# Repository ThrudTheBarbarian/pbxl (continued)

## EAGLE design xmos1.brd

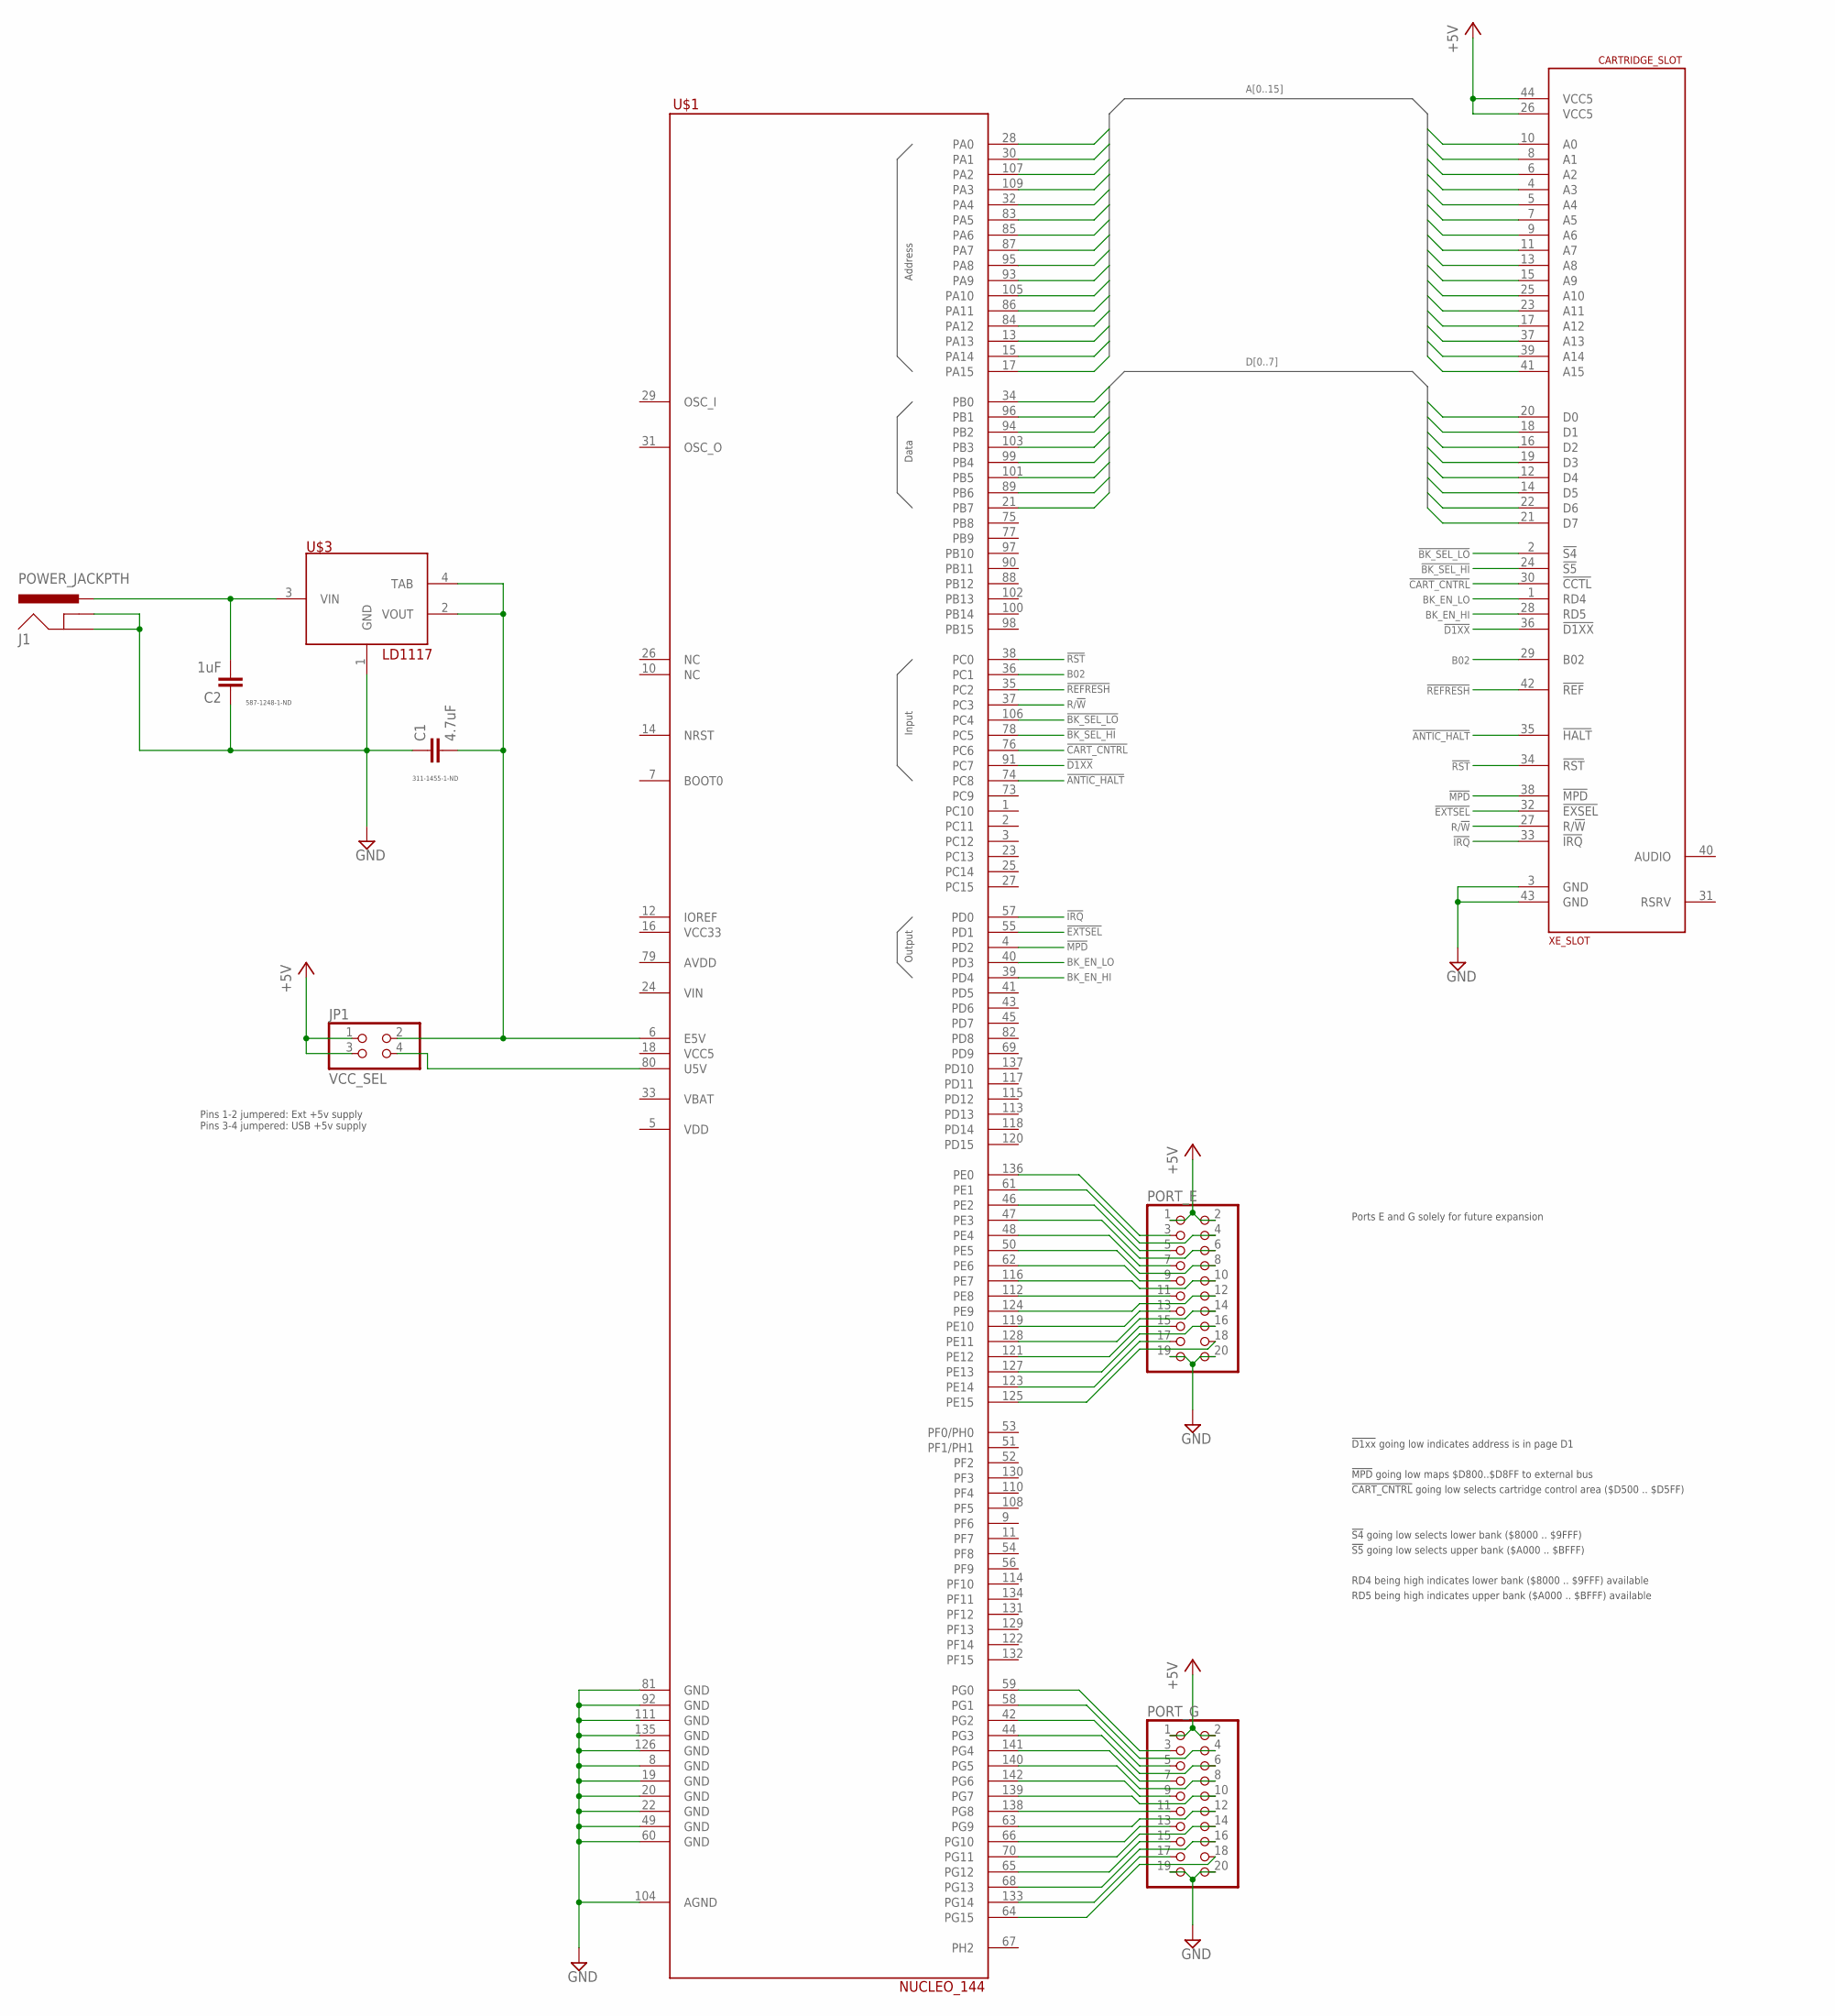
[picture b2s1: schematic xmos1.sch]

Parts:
C1: 4.7uF; C0603
C2: 1uF; C0603
CARTRIDGE_SLOT: XE_SLOT
J1: POWER_JACKPTH; POWER_JACK_PTH
JP1: VCC_SEL; 2X02
PORT_E: PINHD-2X10; 2X10
PORT_G: PINHD-2X10; 2X10
U$1: NUCLEO_144
U$3: LD1117; SOT223

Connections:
!ANTIC_HALT!: CARTRIDGE_SLOT.35 (!HALT!), U$1.74 (PC8)
!BK_SEL_HI!: CARTRIDGE_SLOT.24 (!S5!), U$1.78 (PC5)
!BK_SEL_LO!: CARTRIDGE_SLOT.2 (!S4!), U$1.106 (PC4)
!CART_CNTRL!: CARTRIDGE_SLOT.30 (!CCTL!), U$1.76 (PC6)
!D1XX!: CARTRIDGE_SLOT.36 (!D1XX!), U$1.91 (PC7)
!EXTSEL!: CARTRIDGE_SLOT.32 (!EXSEL!), U$1.55 (PD1)
!IRQ!: CARTRIDGE_SLOT.33 (!IRQ!), U$1.57 (PD0)
!MPD!: CARTRIDGE_SLOT.38 (!MPD!), U$1.4 (PD2)
!REFRESH!: CARTRIDGE_SLOT.42 (!REF!), U$1.35 (PC2)
!RST!: CARTRIDGE_SLOT.34 (!RST!), U$1.38 (PC0)
+5V: CARTRIDGE_SLOT.26 (VCC5), CARTRIDGE_SLOT.44 (VCC5), JP1.1, JP1.3, PORT_E.1, PORT_E.2, PORT_G.1, PORT_G.2
A0: CARTRIDGE_SLOT.10 (A0), U$1.28 (PA0)
A1: CARTRIDGE_SLOT.8 (A1), U$1.30 (PA1)
A2: CARTRIDGE_SLOT.6 (A2), U$1.107 (PA2)
A3: CARTRIDGE_SLOT.4 (A3), U$1.109 (PA3)
A4: CARTRIDGE_SLOT.5 (A4), U$1.32 (PA4)
A5: CARTRIDGE_SLOT.7 (A5), U$1.83 (PA5)
A6: CARTRIDGE_SLOT.9 (A6), U$1.85 (PA6)
A7: CARTRIDGE_SLOT.11 (A7), U$1.87 (PA7)
A8: CARTRIDGE_SLOT.13 (A8), U$1.95 (PA8)
A9: CARTRIDGE_SLOT.15 (A9), U$1.93 (PA9)
A10: CARTRIDGE_SLOT.25 (A10), U$1.105 (PA10)
A11: CARTRIDGE_SLOT.23 (A11), U$1.86 (PA11)
A12: CARTRIDGE_SLOT.17 (A12), U$1.84 (PA12)
A13: CARTRIDGE_SLOT.37 (A13), U$1.13 (PA13)
A14: CARTRIDGE_SLOT.39 (A14), U$1.15 (PA14)
A15: CARTRIDGE_SLOT.41 (A15), U$1.17 (PA15)
B02: CARTRIDGE_SLOT.29 (B02), U$1.36 (PC1)
BK_EN_HI: CARTRIDGE_SLOT.28 (RD5), U$1.39 (PD4)
BK_EN_LO: CARTRIDGE_SLOT.1 (RD4), U$1.40 (PD3)
D0: CARTRIDGE_SLOT.20 (D0), U$1.34 (PB0)
D1: CARTRIDGE_SLOT.18 (D1), U$1.96 (PB1)
D2: CARTRIDGE_SLOT.16 (D2), U$1.94 (PB2)
D3: CARTRIDGE_SLOT.19 (D3), U$1.103 (PB3)
D4: CARTRIDGE_SLOT.12 (D4), U$1.99 (PB4)
D5: CARTRIDGE_SLOT.14 (D5), U$1.101 (PB5)
D6: CARTRIDGE_SLOT.22 (D6), U$1.89 (PB6)
D7: CARTRIDGE_SLOT.21 (D7), U$1.21 (PB7)
GND: C1.1, C2.1, CARTRIDGE_SLOT.3 (GND), CARTRIDGE_SLOT.43 (GND), J1.GND, J1.GNDBREAK, PORT_E.19, PORT_E.20, PORT_G.19, PORT_G.20, U$1.8 (GND), U$1.19 (GND), U$1.20 (GND), U$1.22 (GND), U$1.49 (GND), U$1.60 (GND), U$1.81 (GND), U$1.92 (GND), U$1.104 (AGND), U$1.111 (GND), U$1.126 (GND), U$1.135 (GND), U$3.1 (GND)
unnamed: C1.2, JP1.2, U$1.6 (E5V), U$3.2 (VOUT), U$3.4 (TAB)
unnamed: JP1.4, U$1.80 (U5V)
unnamed: PORT_E.3, U$1.136 (PE0)
unnamed: PORT_E.4, U$1.61 (PE1)
unnamed: PORT_E.5, U$1.46 (PE2)
unnamed: PORT_E.6, U$1.47 (PE3)
unnamed: PORT_E.7, U$1.48 (PE4)
unnamed: PORT_E.8, U$1.50 (PE5)
unnamed: PORT_E.9, U$1.62 (PE6)
unnamed: PORT_E.10, U$1.116 (PE7)
unnamed: PORT_E.11, U$1.112 (PE8)
unnamed: PORT_E.12, U$1.124 (PE9)
unnamed: PORT_E.13, U$1.119 (PE10)
unnamed: PORT_E.14, U$1.128 (PE11)
unnamed: PORT_E.15, U$1.121 (PE12)
unnamed: PORT_E.16, U$1.127 (PE13)
unnamed: PORT_E.17, U$1.123 (PE14)
unnamed: PORT_E.18, U$1.125 (PE15)
unnamed: PORT_G.3, U$1.59 (PG0)
unnamed: PORT_G.4, U$1.58 (PG1)
unnamed: PORT_G.5, U$1.42 (PG2)
unnamed: PORT_G.6, U$1.44 (PG3)
unnamed: PORT_G.7, U$1.141 (PG4)
unnamed: PORT_G.8, U$1.140 (PG5)
unnamed: PORT_G.9, U$1.142 (PG6)
unnamed: PORT_G.11, U$1.138 (PG8)
unnamed: C2.2, J1.PWR, U$3.3 (VIN)
unnamed: PORT_G.12, U$1.63 (PG9)
unnamed: PORT_G.13, U$1.66 (PG10)
unnamed: PORT_G.14, U$1.70 (PG11)
unnamed: PORT_G.15, U$1.65 (PG12)
unnamed: PORT_G.16, U$1.68 (PG13)
unnamed: PORT_G.17, U$1.133 (PG14)
unnamed: PORT_G.18, U$1.64 (PG15)
PORT_G: PORT_G.10, U$1.139 (PG7)
R/!W!: CARTRIDGE_SLOT.27 (R/!W!), U$1.37 (PC3)

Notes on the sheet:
!MPD! going low maps $D800..$D8FF to external bus
!S4! going low selects lower bank ($8000 .. $9FFF)
!S5! going low selects upper bank ($A000 .. $BFFF)
!CART_CNTRL! going low selects cartridge control area ($D500 .. $D5FF)
!D1xx! going low indicates address is in page D1
RD4 being high indicates lower bank ($8000 .. $9FFF) available
RD5 being high indicates upper bank ($A000 .. $BFFF) available
Output
Input
Data
Address
Pins 1-2 jumpered: Ext +5v supply Pins 3-4 jumpered: USB +5v supply
Ports E and G solely for future expansion
311-1455-1-ND
587-1248-1-ND

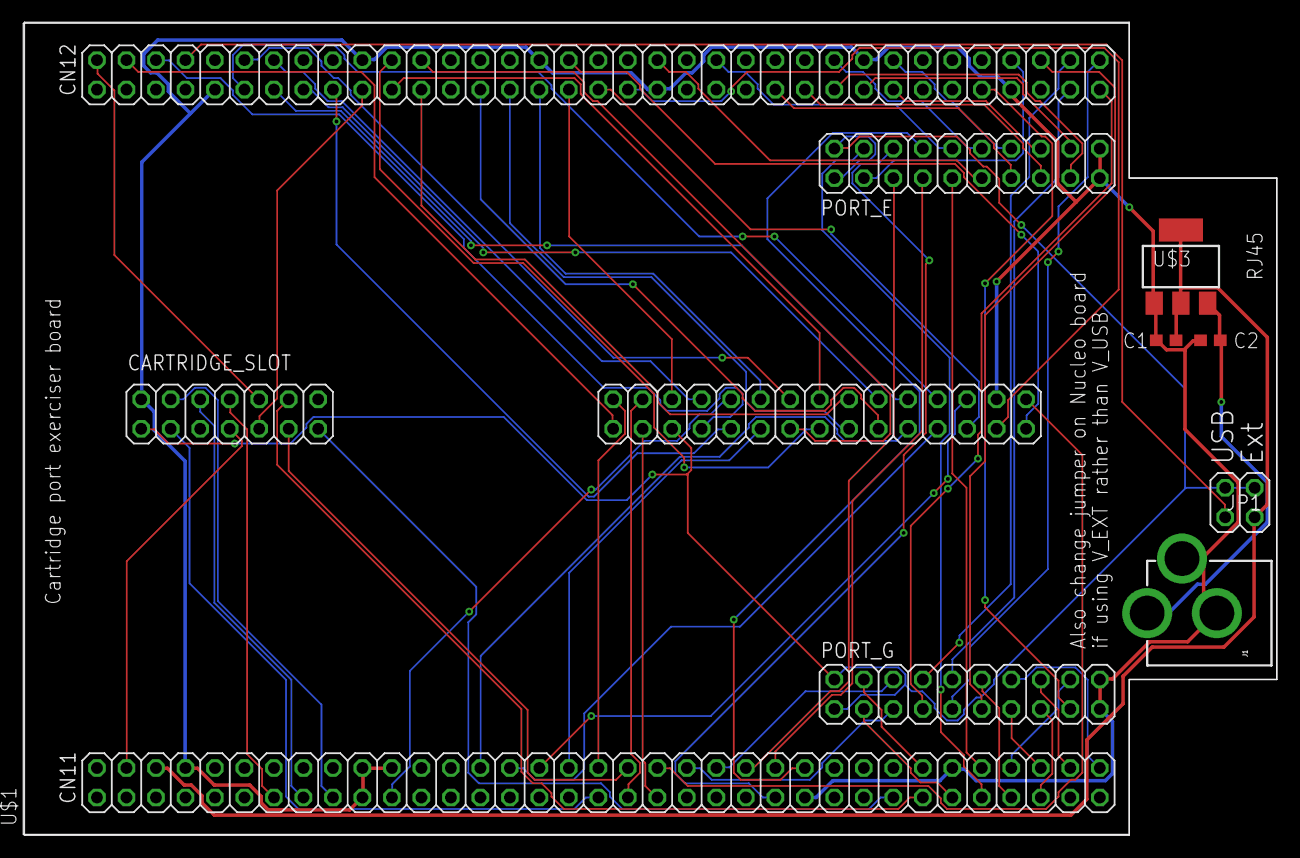
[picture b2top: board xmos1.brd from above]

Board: 2 copper layers, 108.0 x 69.8 mm, 9 parts (0 on the bottom side), 75 nets.

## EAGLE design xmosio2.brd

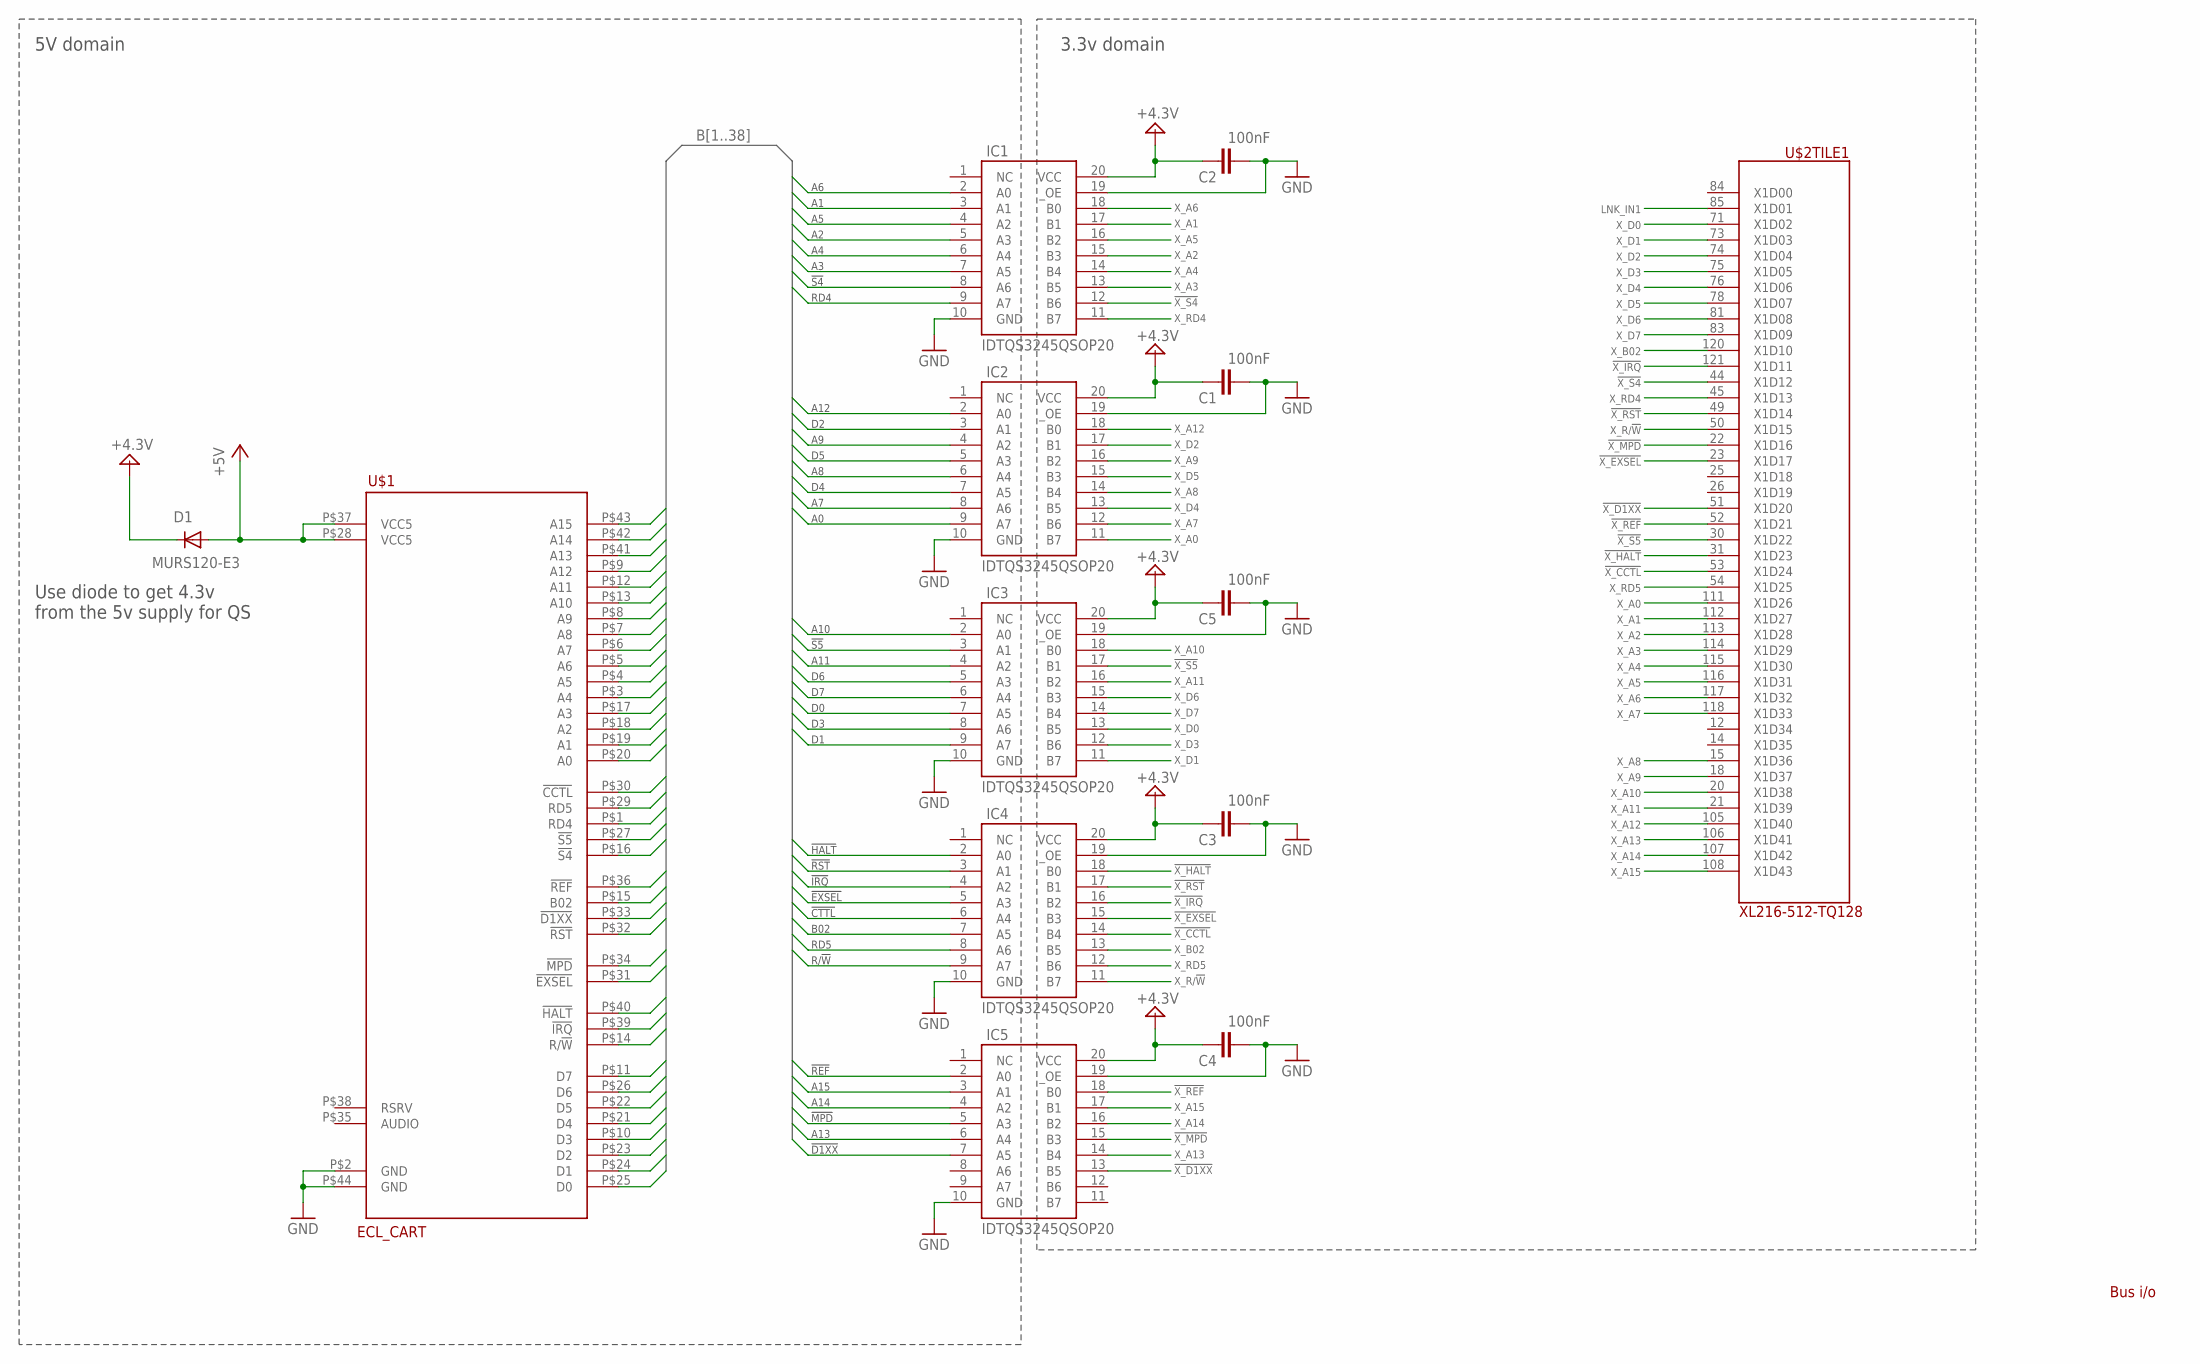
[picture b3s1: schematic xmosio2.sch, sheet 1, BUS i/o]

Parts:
C1, C2, C3, C4, C5: 100nF; C0603
D1: MURS120-E3; SMB
IC1, IC2, IC3, IC4, IC5: IDTQS3245QSOP20; QSOP20
U$1: ECL_CART
U$2: XL216-512-TQ128; TQFP128

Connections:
!X_CCTL!: IC4.14 (B4), U$2.53 (X1D24)
!X_D1XX!: IC5.13 (B5), U$2.51 (X1D20)
!X_EXSEL!: IC4.15 (B3), U$2.23 (X1D17)
!X_HALT!: IC4.18 (B0), U$2.31 (X1D23)
!X_IRQ!: IC4.16 (B2), U$2.121 (X1D11)
!X_MPD!: IC5.15 (B3), U$2.22 (X1D16)
!X_REF!: IC5.18 (B0), U$2.52 (X1D21)
!X_RST!: IC4.17 (B1), U$2.49 (X1D14)
!X_S4!: IC1.12 (B6), U$2.44 (X1D12)
!X_S5!: IC3.17 (B1), U$2.30 (X1D22)
+4.3V: C1.1, C2.1, C3.1, C4.1, C5.1, D1.C, IC1.20 (VCC), IC2.20 (VCC), IC3.20 (VCC), IC4.20 (VCC), IC5.20 (VCC)
+5V: D1.A, U$1.P$28 (VCC5), U$1.P$37 (VCC5); also elsewhere on the board
B1: IC1.9 (A7), U$1.P$1 (RD4)
B2: IC1.8 (A6), U$1.P$16 (!S4!)
B3: IC1.7 (A5), U$1.P$17 (A3)
B4: IC1.6 (A4), U$1.P$3 (A4)
B5: IC1.5 (A3), U$1.P$18 (A2)
B6: IC1.4 (A2), U$1.P$4 (A5)
B7: IC1.3 (A1), U$1.P$19 (A1)
B8: IC1.2 (A0), U$1.P$5 (A6)
B9: IC2.9 (A7), U$1.P$20 (A0)
B10: IC2.8 (A6), U$1.P$6 (A7)
B11: IC2.7 (A5), U$1.P$21 (D4)
B12: IC2.6 (A4), U$1.P$7 (A8)
B13: IC2.5 (A3), U$1.P$22 (D5)
B14: IC2.4 (A2), U$1.P$8 (A9)
B15: IC2.3 (A1), U$1.P$23 (D2)
B16: IC2.2 (A0), U$1.P$9 (A12)
B17: IC3.9 (A7), U$1.P$24 (D1)
B18: IC3.8 (A6), U$1.P$10 (D3)
B19: IC3.7 (A5), U$1.P$25 (D0)
B20: IC3.6 (A4), U$1.P$11 (D7)
B21: IC3.5 (A3), U$1.P$26 (D6)
B22: IC3.4 (A2), U$1.P$12 (A11)
B23: IC3.3 (A1), U$1.P$27 (!S5!)
B24: IC3.2 (A0), U$1.P$13 (A10)
B25: IC4.9 (A7), U$1.P$14 (R/!W!)
B26: IC4.8 (A6), U$1.P$29 (RD5)
B27: IC4.7 (A5), U$1.P$15 (B02)
B28: IC4.6 (A4), U$1.P$30 (!CCTL!)
B29: IC4.5 (A3), U$1.P$31 (!EXSEL!)
B30: IC4.4 (A2), U$1.P$39 (!IRQ!)
B31: IC4.3 (A1), U$1.P$32 (!RST!)
B32: IC4.2 (A0), U$1.P$40 (!HALT!)
B33: IC5.7 (A5), U$1.P$33 (!D1XX!)
B34: IC5.6 (A4), U$1.P$41 (A13)
B35: IC5.5 (A3), U$1.P$34 (!MPD!)
B36: IC5.4 (A2), U$1.P$42 (A14)
B37: IC5.3 (A1), U$1.P$43 (A15)
B38: IC5.2 (A0), U$1.P$36 (!REF!)
GND: C1.2, C2.2, C3.2, C4.2, C5.2, IC1.10 (GND), IC1.19 (_OE), IC2.10 (GND), IC2.19 (_OE), IC3.10 (GND), IC3.19 (_OE), IC4.10 (GND), IC4.19 (_OE), IC5.10 (GND), IC5.19 (_OE), U$1.P$2 (GND), U$1.P$44 (GND); also elsewhere on the board
LNK_IN1: U$2.85 (X1D01); also elsewhere on the board
X_A0: IC2.11 (B7), U$2.111 (X1D26)
X_A1: IC1.17 (B1), U$2.112 (X1D27)
X_A2: IC1.15 (B3), U$2.113 (X1D28)
X_A3: IC1.13 (B5), U$2.114 (X1D29)
X_A4: IC1.14 (B4), U$2.115 (X1D30)
X_A5: IC1.16 (B2), U$2.116 (X1D31)
X_A6: IC1.18 (B0), U$2.117 (X1D32)
X_A7: IC2.12 (B6), U$2.118 (X1D33)
X_A8: IC2.14 (B4), U$2.15 (X1D36)
X_A9: IC2.16 (B2), U$2.18 (X1D37)
X_A10: IC3.18 (B0), U$2.20 (X1D38)
X_A11: IC3.16 (B2), U$2.21 (X1D39)
X_A12: IC2.18 (B0), U$2.105 (X1D40)
X_A13: IC5.14 (B4), U$2.106 (X1D41)
X_A14: IC5.16 (B2), U$2.107 (X1D42)
X_A15: IC5.17 (B1), U$2.108 (X1D43)
X_B02: IC4.13 (B5), U$2.120 (X1D10)
X_D0: IC3.13 (B5), U$2.71 (X1D02)
X_D1: IC3.11 (B7), U$2.73 (X1D03)
X_D2: IC2.17 (B1), U$2.74 (X1D04)
X_D3: IC3.12 (B6), U$2.75 (X1D05)
X_D4: IC2.13 (B5), U$2.76 (X1D06)
X_D5: IC2.15 (B3), U$2.78 (X1D07)
X_D6: IC3.15 (B3), U$2.81 (X1D08)
X_D7: IC3.14 (B4), U$2.83 (X1D09)
X_R/!W!: IC4.11 (B7), U$2.50 (X1D15)
X_RD4: IC1.11 (B7), U$2.45 (X1D13)
X_RD5: IC4.12 (B6), U$2.54 (X1D25)

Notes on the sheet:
A15
A14
A13
A12
A11
A10
!CTTL!
B02
RD5
RD4
!S5!
!S4!
!REF!
!D1XX!
!RST!
!MPD!
!EXSEL!
!HALT!
!IRQ!
R/!W!
Bus i/o
5V domain
3.3v domain
Use diode to get 4.3v from the 5v supply for QS

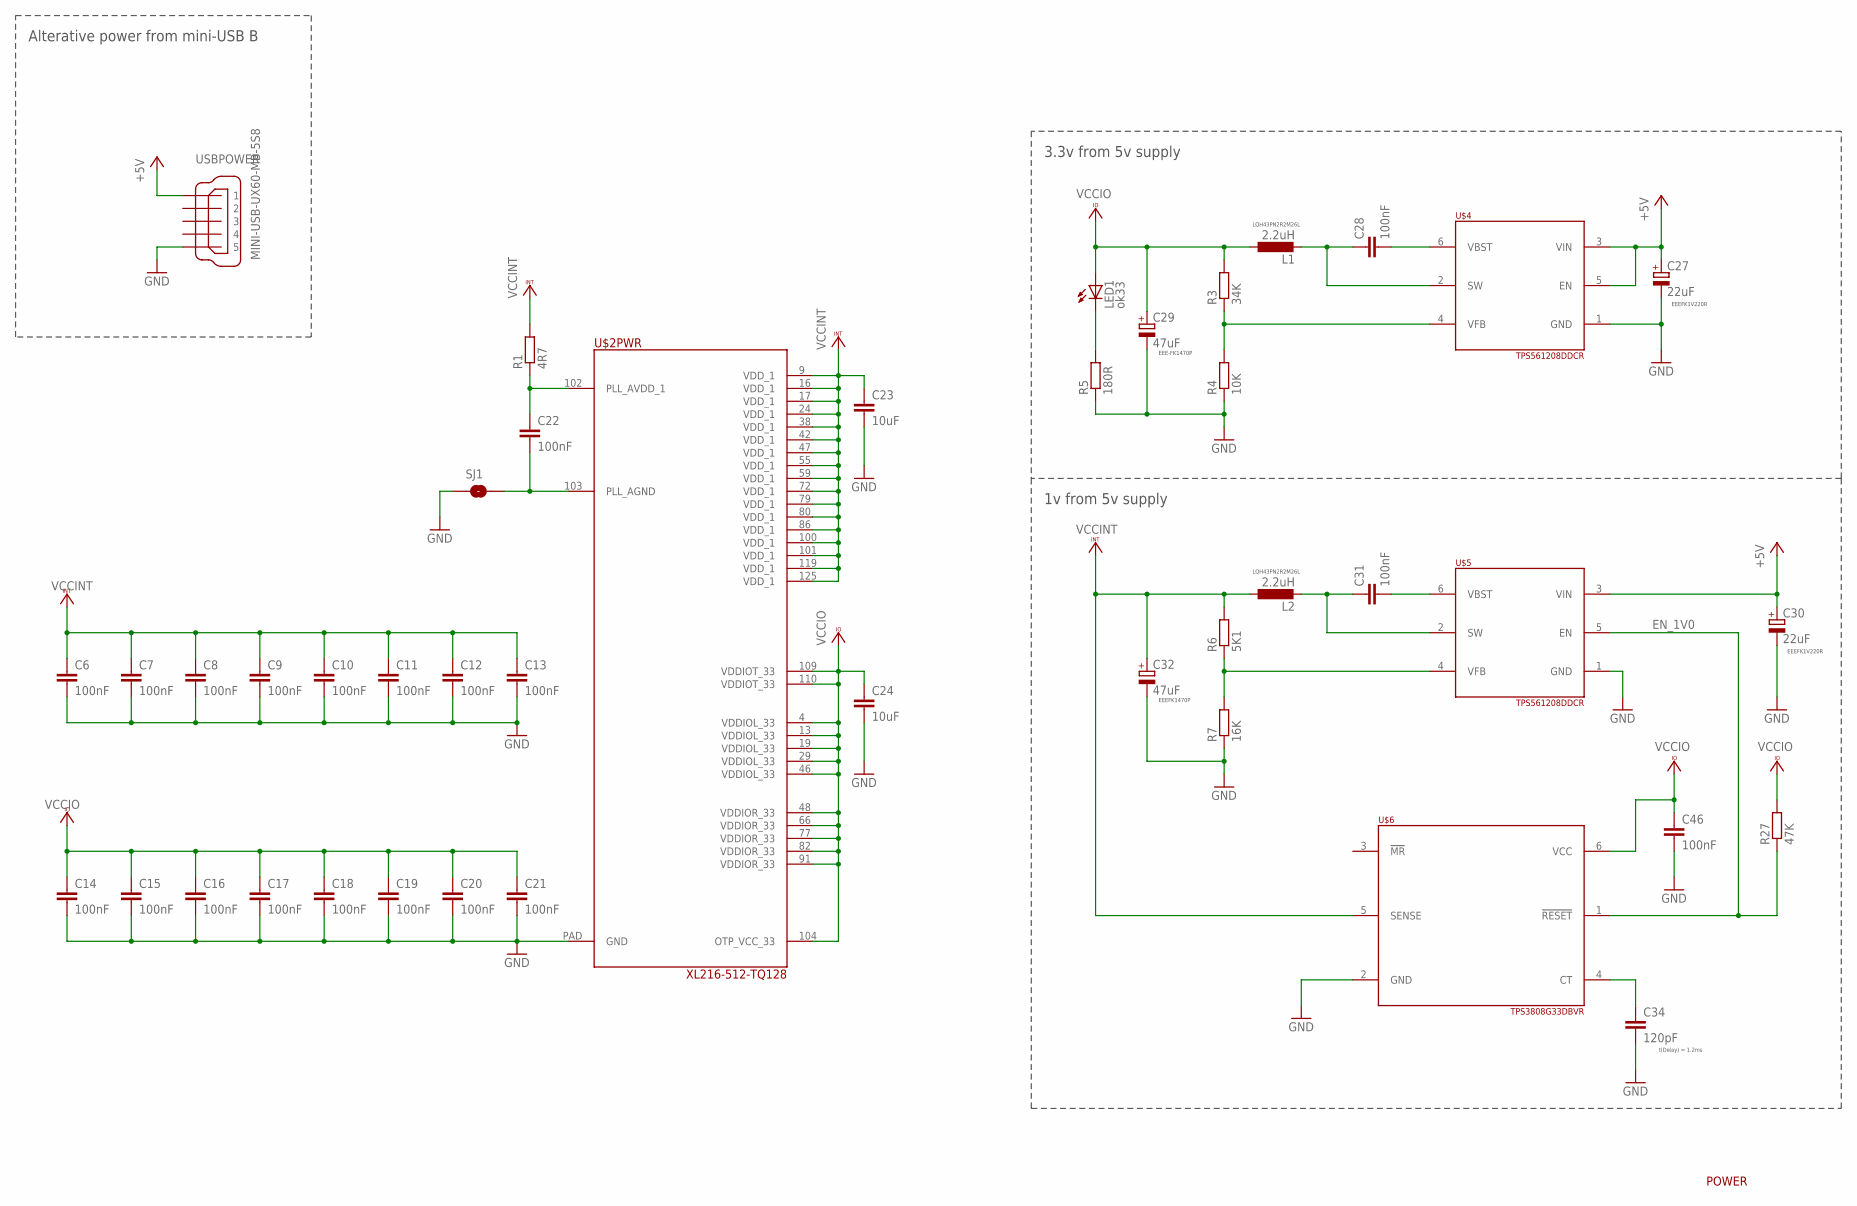
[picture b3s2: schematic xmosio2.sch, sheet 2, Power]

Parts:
C6, C7, C8, C9, C10, C11, C12, C13, C14, C15, C16, C17, C18, C19, C20, C21, C22, C28, C31, C46: 100nF; C0603
C23, C24: 10uF; C0603
C27, C30: 22uF; PANASONIC_C
C29, C32: 47uF; PANASONIC_D
C34: 120pF; C0603
L1, L2: 2.2uH; L1812
LED1: ok33; CHIP-LED0805
R1: 4R7; R0603
R3: 34K; R0603
R4: 10K; R0603
R5: 180R; R0603
R6: 5K1; R0603
R7: 16K; R0603
R27: 47K; R0603
SJ1: SOLDERJUMPERNC; SJ_2S
U$2: XL216-512-TQ128; TQFP128
U$4, U$5: TPS561208DDCR; TSOT23-6_DDC
U$6: TPS3808G33DBVR; SOT23-6
USBPOWER: MINI-USB-UX60-MB-5S8; UX60-MB-5S8

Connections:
+5V: C27.+, C30.+, U$4.3 (VIN), U$4.5 (EN), U$5.3 (VIN), USBPOWER.1; also elsewhere on the board
EN_1V0: R27.1, U$5.5 (EN), U$6.1 (!RESET!)
GND: C6.2, C7.2, C8.2, C9.2, C10.2, C11.2, C12.2, C13.2, C14.2, C15.2, C16.2, C17.2, C18.2, C19.2, C20.2, C21.2, C23.2, C24.2, C27.-, C29.-, C30.-, C32.-, C34.2, C46.2, R4.1, R5.1, R7.1, SJ1.1, U$2.PAD (GND), U$4.1 (GND), U$5.1 (GND), U$6.2 (GND), USBPOWER.5; also elsewhere on the board
unnamed: C22.1, R1.1, U$2.102 (PLL_AVDD_1)
unnamed: C22.2, SJ1.2, U$2.103 (PLL_AGND)
unnamed: C28.2, U$4.6 (VBST)
unnamed: C28.1, L1.2, U$4.2 (SW)
unnamed: C31.2, U$5.6 (VBST)
unnamed: R3.1, R4.2, U$4.4 (VFB)
unnamed: LED1.C, R5.2
unnamed: C31.1, L2.2, U$5.2 (SW)
unnamed: R6.1, R7.2, U$5.4 (VFB)
unnamed: C34.1, U$6.4 (CT)
VCCINT: C6.1, C7.1, C8.1, C9.1, C10.1, C11.1, C12.1, C13.1, C23.1, C32.+, L2.1, R1.2, R6.2, U$2.9 (VDD_1), U$2.16 (VDD_1), U$2.17 (VDD_1), U$2.24 (VDD_1), U$2.38 (VDD_1), U$2.42 (VDD_1), U$2.47 (VDD_1), U$2.55 (VDD_1), U$2.59 (VDD_1), U$2.72 (VDD_1), U$2.79 (VDD_1), U$2.80 (VDD_1), U$2.86 (VDD_1), U$2.100 (VDD_1), U$2.101 (VDD_1), U$2.119 (VDD_1), U$2.125 (VDD_1), U$6.5 (SENSE); also elsewhere on the board
VCCIO: C14.1, C15.1, C16.1, C17.1, C18.1, C19.1, C20.1, C21.1, C24.1, C29.+, C46.1, L1.1, LED1.A, R3.2, R27.2, U$2.4 (VDDIOL_33), U$2.13 (VDDIOL_33), U$2.19 (VDDIOL_33), U$2.29 (VDDIOL_33), U$2.46 (VDDIOL_33), U$2.48 (VDDIOR_33), U$2.66 (VDDIOR_33), U$2.77 (VDDIOR_33), U$2.82 (VDDIOR_33), U$2.91 (VDDIOR_33), U$2.104 (OTP_VCC_33), U$2.109 (VDDIOT_33), U$2.110 (VDDIOT_33), U$6.6 (VCC); also elsewhere on the board

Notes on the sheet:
EEEFK1V220R
LQH43PN2R2M26L
EEE-FK1470P
3.3v from 5v supply
EEEFK1470P
1v from 5v supply
t(Delay) = 1.2ms
POWER
Alterative power from mini-USB B

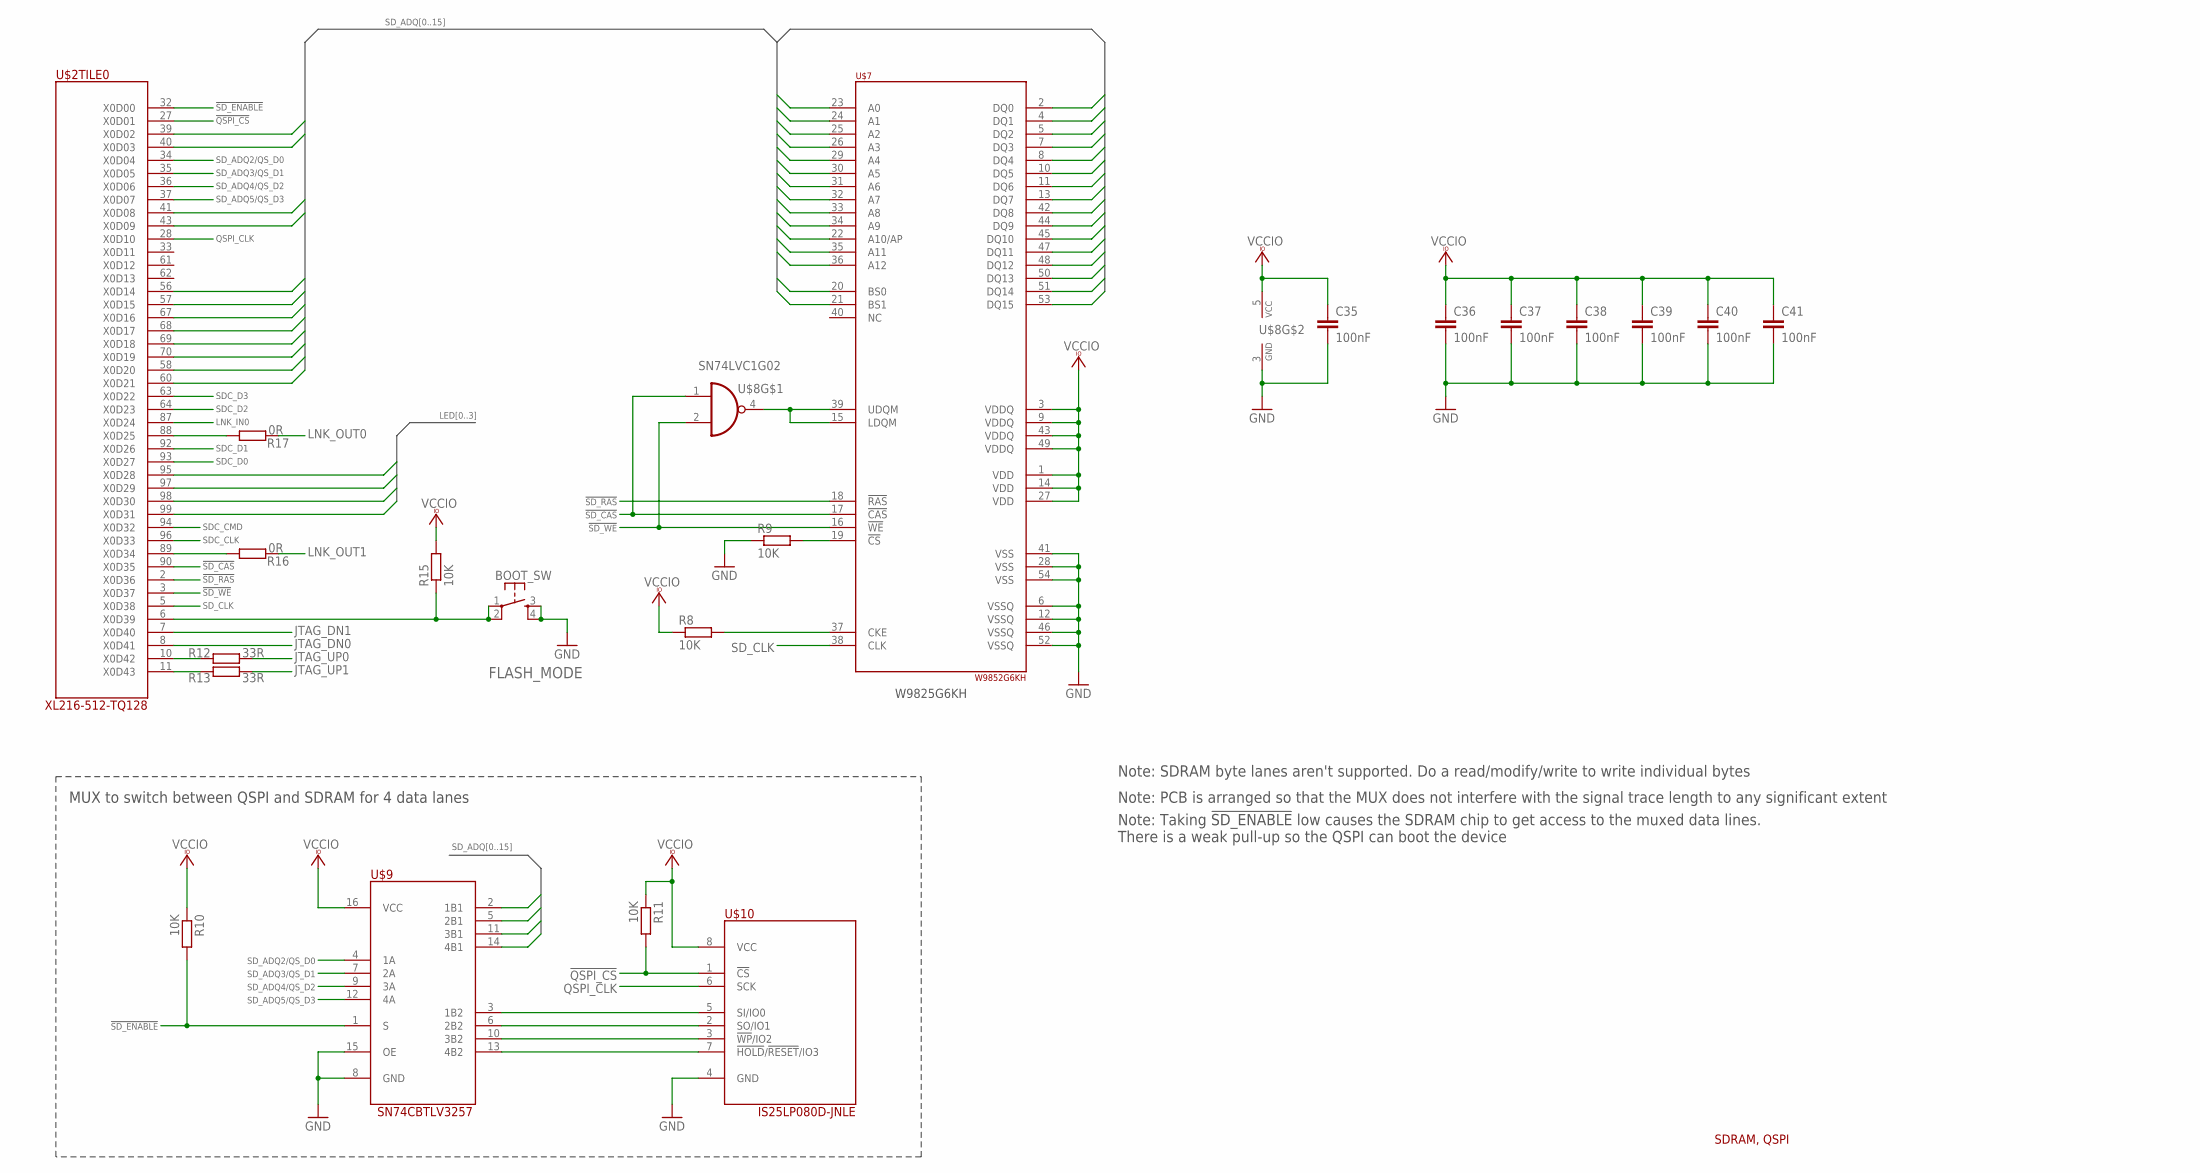
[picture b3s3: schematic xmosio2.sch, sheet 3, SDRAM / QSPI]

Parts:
BOOT_SW: FLASH_MODE; TACTILE-PTH
C35, C36, C37, C38, C39, C40, C41: 100nF; C0603
R8, R9, R10, R11, R15: 10K; R0603
R12, R13: 33R; R0603
R16, R17: 0R; R0603
U$2: XL216-512-TQ128; TQFP128
U$7: W9852G6KH; TSOP54-400
U$8: SN74LVC1G02; SOT23-5
U$9: SN74CBTLV3257; SO16
U$10: IS25LP080D-JNLE; SO-08

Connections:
!QSPI_CS!: R11.2, U$2.27 (X0D01), U$10.1 (!CS!)
!SD_CAS!: U$2.90 (X0D35), U$7.17 (!CAS!), U$8.1 (I0)
!SD_ENABLE!: R10.2, U$2.32 (X0D00), U$9.1 (S)
!SD_RAS!: U$2.2 (X0D36), U$7.18 (!RAS!)
!SD_WE!: U$2.3 (X0D37), U$7.16 (!WE!), U$8.2 (I1)
GND: BOOT_SW.3, BOOT_SW.4, C35.2, C36.2, C37.2, C38.2, C39.2, C40.2, C41.2, R9.1, U$7.6 (VSSQ), U$7.12 (VSSQ), U$7.28 (VSS), U$7.41 (VSS), U$7.46 (VSSQ), U$7.52 (VSSQ), U$7.54 (VSS), U$8.3 (GND), U$9.8 (GND), U$9.15 (OE), U$10.4 (GND); also elsewhere on the board
JTAG_DN0: U$2.8 (X0D41); also elsewhere on the board
JTAG_DN1: U$2.7 (X0D40); also elsewhere on the board
JTAG_UP0: R12.2; also elsewhere on the board
JTAG_UP1: R13.2; also elsewhere on the board
LED0: U$2.95 (X0D28); also elsewhere on the board
LED1: U$2.97 (X0D29); also elsewhere on the board
LED2: U$2.98 (X0D30); also elsewhere on the board
LED3: U$2.99 (X0D31); also elsewhere on the board
LNK_IN0: U$2.87 (X0D24); also elsewhere on the board
LNK_OUT0: R17.2; also elsewhere on the board
LNK_OUT1: R16.2; also elsewhere on the board
unnamed: U$7.15 (LDQM), U$7.39 (UDQM), U$8.4 (O)
unnamed: R8.2, U$7.37 (CKE)
unnamed: U$9.3 (1B2), U$10.5 (SI/IO0)
unnamed: R9.2, U$7.19 (!CS!)
unnamed: U$9.6 (2B2), U$10.2 (SO/IO1)
unnamed: U$9.10 (3B2), U$10.3 (!WP!/IO2)
unnamed: U$9.13 (4B2), U$10.7 (!HOLD!/!RESET!/IO3)
unnamed: R12.1, U$2.10 (X0D42)
unnamed: R13.1, U$2.11 (X0D43)
unnamed: R17.1, U$2.88 (X0D25)
unnamed: R16.1, U$2.89 (X0D34)
unnamed: BOOT_SW.1, BOOT_SW.2, R15.1, U$2.6 (X0D39)
QSPI_CLK: U$2.28 (X0D10), U$10.6 (SCK)
SDC_CLK: U$2.96 (X0D33); also elsewhere on the board
SDC_CMD: U$2.94 (X0D32); also elsewhere on the board
SDC_D0: U$2.93 (X0D27); also elsewhere on the board
SDC_D1: U$2.92 (X0D26); also elsewhere on the board
SDC_D2: U$2.64 (X0D23); also elsewhere on the board
SDC_D3: U$2.63 (X0D22); also elsewhere on the board
SD_ADQ0: U$2.39 (X0D02), U$7.2 (DQ0), U$7.23 (A0)
SD_ADQ1: U$2.40 (X0D03), U$7.4 (DQ1), U$7.24 (A1)
SD_ADQ2: U$7.5 (DQ2), U$7.25 (A2), U$9.2 (1B1)
SD_ADQ2/QS_D0: U$2.34 (X0D04), U$9.4 (1A)
SD_ADQ3: U$7.7 (DQ3), U$7.26 (A3), U$9.5 (2B1)
SD_ADQ3/QS_D1: U$2.35 (X0D05), U$9.7 (2A)
SD_ADQ4: U$7.8 (DQ4), U$7.29 (A4), U$9.11 (3B1)
SD_ADQ4/QS_D2: U$2.36 (X0D06), U$9.9 (3A)
SD_ADQ5: U$7.10 (DQ5), U$7.30 (A5), U$9.14 (4B1)
SD_ADQ5/QS_D3: U$2.37 (X0D07), U$9.12 (4A)
SD_ADQ6: U$2.41 (X0D08), U$7.11 (DQ6), U$7.31 (A6)
SD_ADQ7: U$2.43 (X0D09), U$7.13 (DQ7), U$7.32 (A7)
SD_ADQ8: U$2.56 (X0D14), U$7.33 (A8), U$7.42 (DQ8)
SD_ADQ9: U$2.57 (X0D15), U$7.34 (A9), U$7.44 (DQ9)
SD_ADQ10: U$2.67 (X0D16), U$7.22 (A10/AP), U$7.45 (DQ10)
SD_ADQ11: U$2.68 (X0D17), U$7.35 (A11), U$7.47 (DQ11)
SD_ADQ12: U$2.69 (X0D18), U$7.36 (A12), U$7.48 (DQ12)
SD_ADQ13: U$2.70 (X0D19), U$7.20 (BS0), U$7.50 (DQ13)
SD_ADQ14: U$2.58 (X0D20), U$7.21 (BS1), U$7.51 (DQ14)
SD_ADQ15: U$2.60 (X0D21), U$7.53 (DQ15)
SD_CLK: U$2.5 (X0D38), U$7.38 (CLK)
VCCIO: C35.1, C36.1, C37.1, C38.1, C39.1, C40.1, C41.1, R8.1, R10.1, R11.1, R15.2, U$7.1 (VDD), U$7.3 (VDDQ), U$7.9 (VDDQ), U$7.14 (VDD), U$7.27 (VDD), U$7.43 (VDDQ), U$7.49 (VDDQ), U$8.5 (VCC), U$9.16 (VCC), U$10.8 (VCC); also elsewhere on the board

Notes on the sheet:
Note: Taking !SD_ENABLE! low causes the SDRAM chip to get access to the muxed data lines. There is a weak pull-up so the QSPI can boot the device
SDRAM, QSPI
MUX to switch between QSPI and SDRAM for 4 data lanes
Note: PCB is arranged so that the MUX does not interfere with the signal trace length to any significant extent
Note: SDRAM byte lanes aren't supported. Do a read/modify/write to write individual bytes
W9825G6KH
